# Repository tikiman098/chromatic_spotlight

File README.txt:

chromatic_spotlight
===================

Camera ring LED array

This is a high power LED driver PCB that is designed to power monochromatic LED's in a ring around a camera.

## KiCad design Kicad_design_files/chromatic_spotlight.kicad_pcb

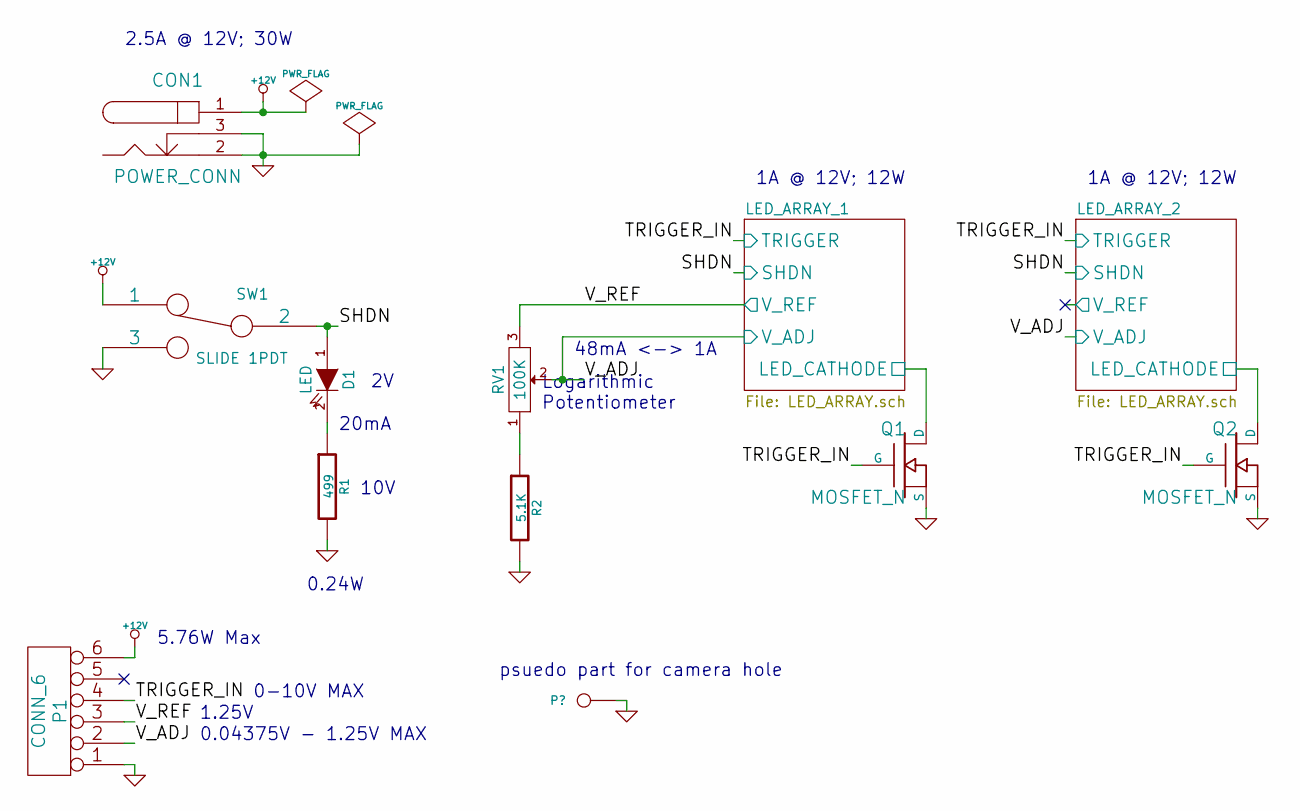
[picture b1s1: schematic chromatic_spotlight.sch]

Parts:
CON1: POWER_CONN
D1: LED
P1: CONN_6
Q1, Q2: MOSFET_N
R1: 499
R2: 5.1K
RV1: 100K
SW1: SLIDE 1PDT

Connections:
+12V: CON1.1, P1.6, SW1.1; also elsewhere on the board
/LED_ARRAY_1/LED_CATHODE: Q1.3 (D); also elsewhere on the board
/LED_ARRAY_1/SHDN: D1.1 (A), SW1.2; also elsewhere on the board
/LED_ARRAY_1/TRIGGER: P1.4, Q1.1 (G), Q2.1 (G); also elsewhere on the board
/LED_ARRAY_1/V_ADJ: P1.2, RV1.2; also elsewhere on the board
/LED_ARRAY_1/V_REF: P1.3, RV1.3; also elsewhere on the board
/LED_ARRAY_2/LED_CATHODE: Q2.3 (D); also elsewhere on the board
GND: CON1.2, CON1.3, P1.1, Q1.2 (S), Q2.2 (S), R1.2, R2.2, SW1.3; also elsewhere on the board
unnamed: D1.2 (K), R1.1
unnamed: R2.1, RV1.1

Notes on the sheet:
0-10V MAX
48mA <-> 1A
Logarithmic Potentiometer
20mA
10V
0.24W
1A @ 12V; 12W
2.5A @ 12V; 30W
5.76W Max
1.25V
0.04375V - 1.25V MAX
psuedo part for camera hole

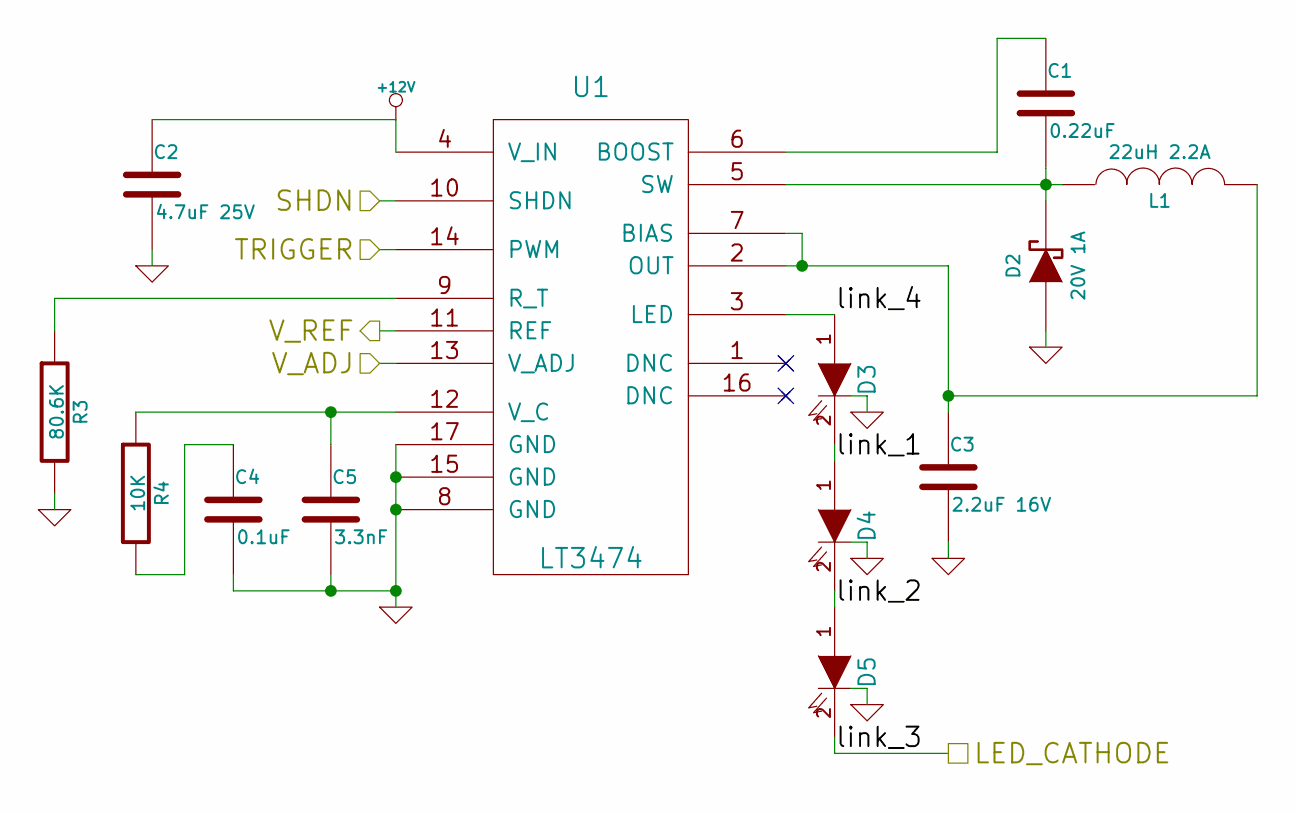
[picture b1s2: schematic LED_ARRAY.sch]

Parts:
C1: 0.22uF
C2: 4.7uF 25V
C3: 2.2uF 16V
C4: 0.1uF
C5: 3.3nF
D2: 20V 1A
D3, D4, D5: XP-E2_LED
L1: 22uH 2.2A
R3: 80.6K
R4: 10K
U1: LT3474

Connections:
+12V: C2.1, U1.4 (V_IN); also elsewhere on the board
/LED_ARRAY_1/LED_CATHODE: D5.2 (K); also elsewhere on the board
/LED_ARRAY_1/SHDN: U1.10 (SHDN); also elsewhere on the board
/LED_ARRAY_1/TRIGGER: U1.14 (PWM); also elsewhere on the board
/LED_ARRAY_1/V_ADJ: U1.13 (V_ADJ); also elsewhere on the board
/LED_ARRAY_1/V_REF: U1.11 (REF); also elsewhere on the board
/LED_ARRAY_1/link_1: D3.2 (K), D4.1 (A)
/LED_ARRAY_1/link_2: D4.2 (K), D5.1 (A)
/LED_ARRAY_1/link_4: D3.1 (A), U1.3 (LED)
GND: C2.2, C3.2, C4.2, C5.2, D2.1 (A), D3.3 (thermal_isloated), D4.3 (thermal_isloated), D5.3 (thermal_isloated), R3.2, U1.8 (GND), U1.15 (GND), U1.17 (GND); also elsewhere on the board
unnamed: C1.1, U1.6 (BOOST)
unnamed: C1.2, D2.2 (K), L1.1, U1.5 (SW)
unnamed: C3.1, L1.2, U1.2 (OUT), U1.7 (BIAS)
unnamed: R3.1, U1.9 (R_T)
unnamed: C4.1, R4.2
unnamed: C5.1, R4.1, U1.12 (V_C)

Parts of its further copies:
C6: 0.22uF
C7: 4.7uF 25V
C8: 2.2uF 16V
C9: 0.1uF
C10: 3.3nF
D6: 20V 1A
D7, D8, D9: XP-E2_LED
L2: 22uH 2.2A
R5: 80.6K
R6: 10K
U2: LT3474

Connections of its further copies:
+12V: C7.1, U2.4 (V_IN); also elsewhere on the board
/LED_ARRAY_1/SHDN: U2.10 (SHDN); also elsewhere on the board
/LED_ARRAY_1/TRIGGER: U2.14 (PWM); also elsewhere on the board
/LED_ARRAY_1/V_ADJ: U2.13 (V_ADJ); also elsewhere on the board
/LED_ARRAY_2/LED_CATHODE: D9.2 (K); also elsewhere on the board
/LED_ARRAY_2/link_1: D7.2 (K), D8.1 (A)
/LED_ARRAY_2/link_2: D8.2 (K), D9.1 (A)
/LED_ARRAY_2/link_4: D7.1 (A), U2.3 (LED)
GND: C7.2, C8.2, C9.2, C10.2, D6.1 (A), D7.3 (thermal_isloated), D8.3 (thermal_isloated), D9.3 (thermal_isloated), R5.2, U2.8 (GND), U2.15 (GND), U2.17 (GND); also elsewhere on the board
unnamed: C6.1, U2.6 (BOOST)
unnamed: C6.2, D6.2 (K), L2.1, U2.5 (SW)
unnamed: C8.1, L2.2, U2.2 (OUT), U2.7 (BIAS)
unnamed: R5.1, U2.9 (R_T)
unnamed: C9.1, R6.2
unnamed: C10.1, R6.1, U2.12 (V_C)

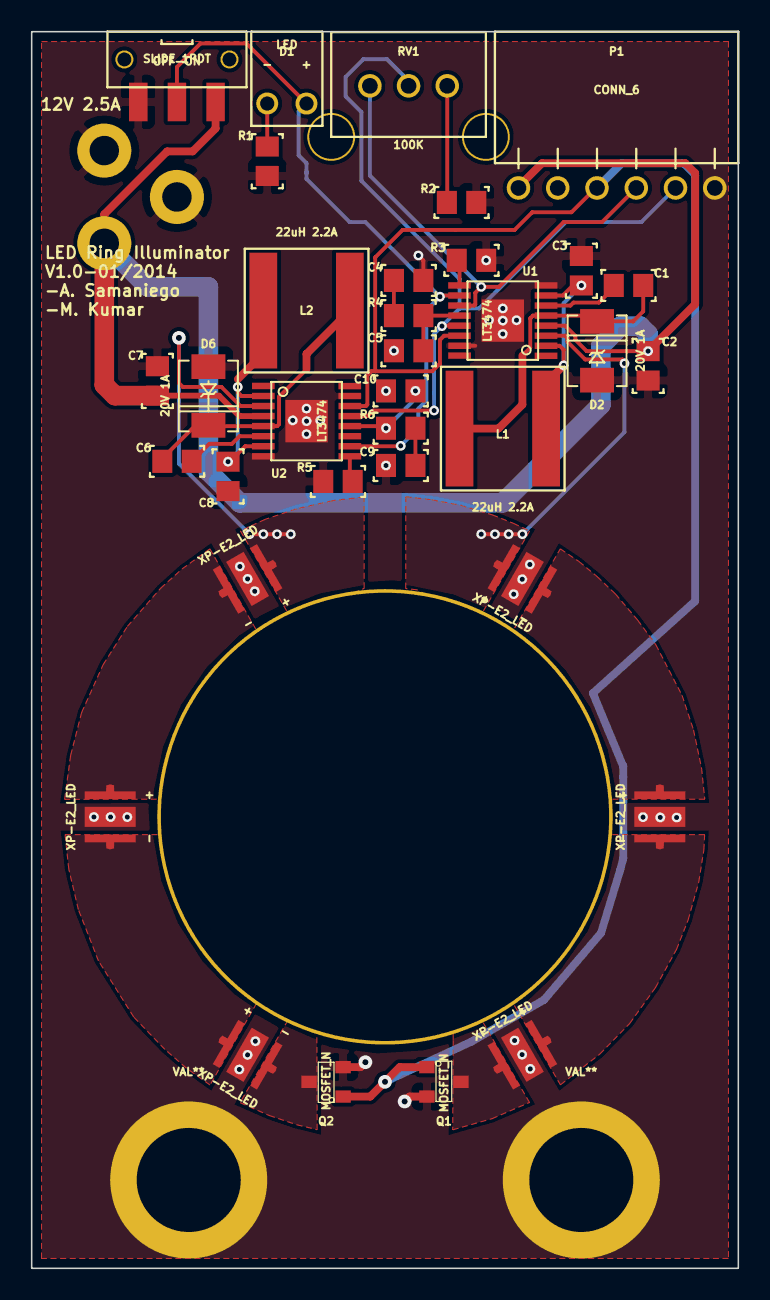
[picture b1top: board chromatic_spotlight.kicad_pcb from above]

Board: 2 copper layers, 45.7 x 80.0 mm, 38 parts (1 on the bottom side), 28 nets.

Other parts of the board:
1,4-20_screw, 1,4-20_screw#2: VAL**; 1,4-20_screw
Camera_hole: VAL**; Camera_hole
OFF-ON: SLIDE 1PDT; SW_SPDT_slide_SMT

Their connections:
+12V: OFF-ON.1; also elsewhere on the board
/LED_ARRAY_1/SHDN: OFF-ON.2; also elsewhere on the board
GND: 1,4-20_screw.1, 1,4-20_screw#2.1, Camera_hole.1, OFF-ON.3; also elsewhere on the board

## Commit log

2014-01-15 setup
2014-01-15 initial kicad files
2014-01-15 almost done with layout
2014-01-16 added numerous improvements
2014-01-16 layout completed
    gonna let it sit for the night before exporting
2014-01-16 going home for the night
2014-01-16 reviewed, added screw holes
2014-01-16 going to try to reset global texts
2014-01-16 added manufacturing files
2014-01-16 final v1 sending to manufacture
2014-01-16 fixed minor manufacturing issues
2014-01-16 added some previews
